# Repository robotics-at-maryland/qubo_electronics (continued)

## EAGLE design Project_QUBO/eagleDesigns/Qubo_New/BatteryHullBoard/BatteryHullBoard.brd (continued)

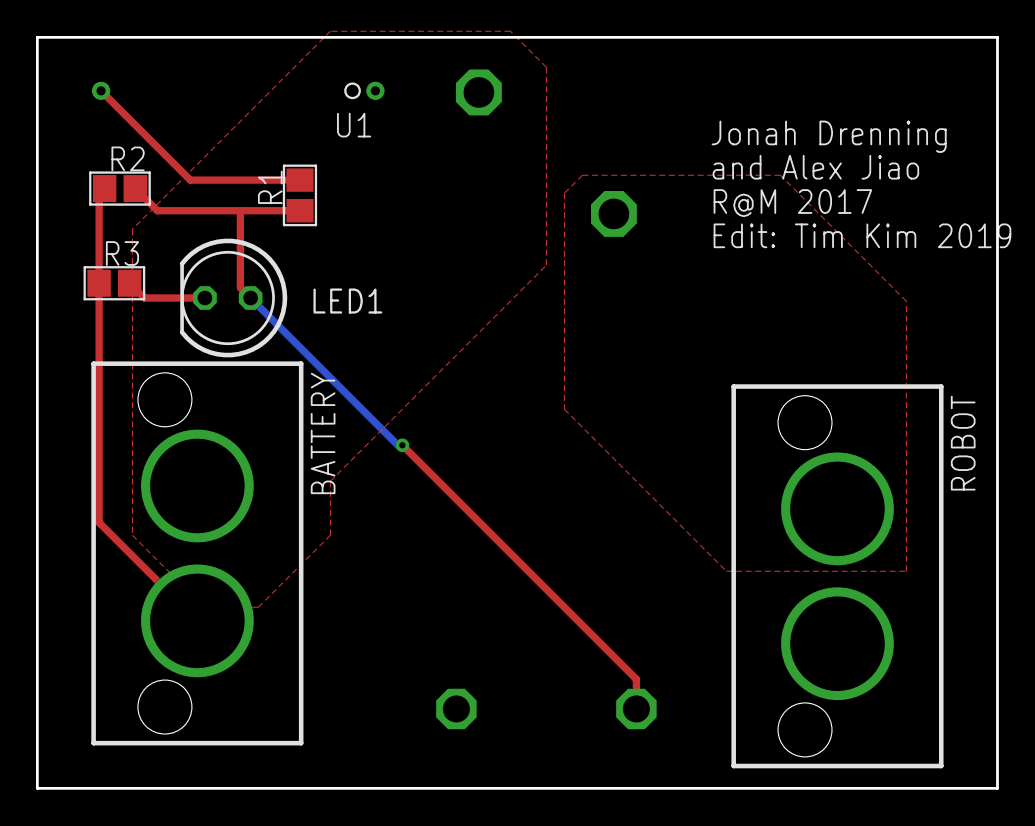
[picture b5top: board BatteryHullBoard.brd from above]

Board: 2 copper layers, 53.3 x 41.7 mm, 8 parts (0 on the bottom side), 6 nets.

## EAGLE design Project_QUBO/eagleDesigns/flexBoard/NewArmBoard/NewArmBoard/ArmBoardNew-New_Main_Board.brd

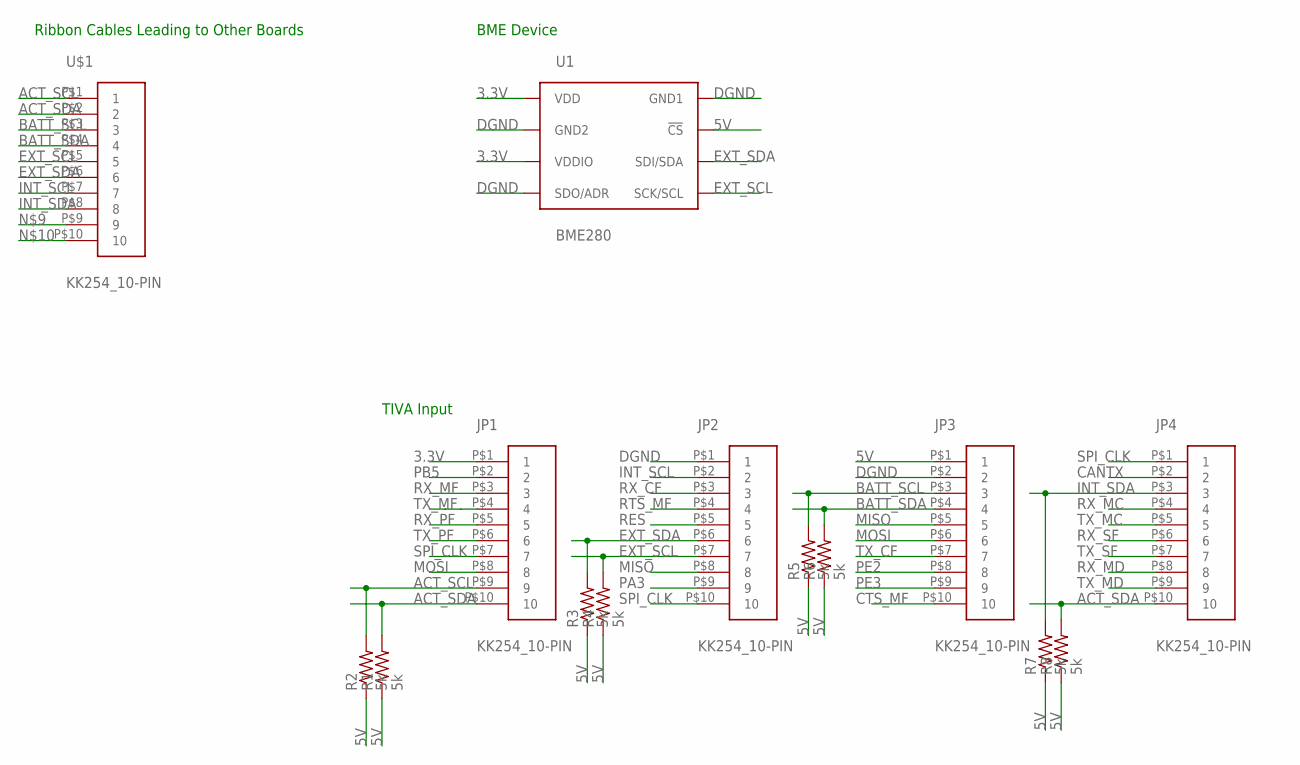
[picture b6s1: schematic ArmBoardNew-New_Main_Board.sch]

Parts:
JP1, JP2, JP3, JP4: KK254_10-PIN
R1, R2, R3, R4, R5, R6, R7, R8: 5k; R0805
U1: BME280; BME280_LGA
U$1: KK254_10-PIN

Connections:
3.3V: JP1.P$1 (1), U1.P$6 (VDDIO), U1.P$8 (VDD)
5V: JP3.P$1 (1), R1.1, R2.1, R3.1, R4.1, R5.1, R6.1, R7.1, R8.1, U1.P$2 (!CS)
ACT_SCL: JP1.P$9 (9), R2.2, U$1.P$1 (1)
ACT_SDA: JP1.P$10 (10), JP4.P$10 (10), R1.2, R8.2, U$1.P$2 (2)
BATT_SCL: JP3.P$3 (3), R5.2, U$1.P$3 (3)
BATT_SDA: JP3.P$4 (4), R6.2, U$1.P$4 (4)
CANTX: JP4.P$2 (2)
CTS_MF: JP3.P$10 (10)
DGND: JP2.P$1 (1), JP3.P$2 (2), U1.P$1 (GND1), U1.P$5 (SDO/ADR), U1.P$7 (GND2)
EXT_SCL: JP2.P$7 (7), R4.2, U1.P$4 (SCK/SCL), U$1.P$5 (5)
EXT_SDA: JP2.P$6 (6), R3.2, U1.P$3 (SDI/SDA), U$1.P$6 (6)
INT_SCL: JP2.P$2 (2), U$1.P$7 (7)
INT_SDA: JP4.P$3 (3), R7.2, U$1.P$8 (8)
MISO: JP2.P$8 (8), JP3.P$5 (5)
MOSI: JP1.P$8 (8), JP3.P$6 (6)
PA3: JP2.P$9 (9)
PB5: JP1.P$2 (2)
PE2: JP3.P$8 (8)
PE3: JP3.P$9 (9)
RES: JP2.P$5 (5)
RTS_MF: JP2.P$4 (4)
RX_CF: JP2.P$3 (3)
RX_MC: JP4.P$4 (4)
RX_MD: JP4.P$8 (8)
RX_MF: JP1.P$3 (3)
RX_PF: JP1.P$5 (5)
RX_SF: JP4.P$6 (6)
SPI_CLK: JP1.P$7 (7), JP2.P$10 (10), JP4.P$1 (1)
TX_CF: JP3.P$7 (7)
TX_MC: JP4.P$5 (5)
TX_MD: JP4.P$9 (9)
TX_MF: JP1.P$4 (4)
TX_PF: JP1.P$6 (6)
TX_SF: JP4.P$7 (7)

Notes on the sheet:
TIVA Input
Ribbon Cables Leading to Other Boards
BME Device

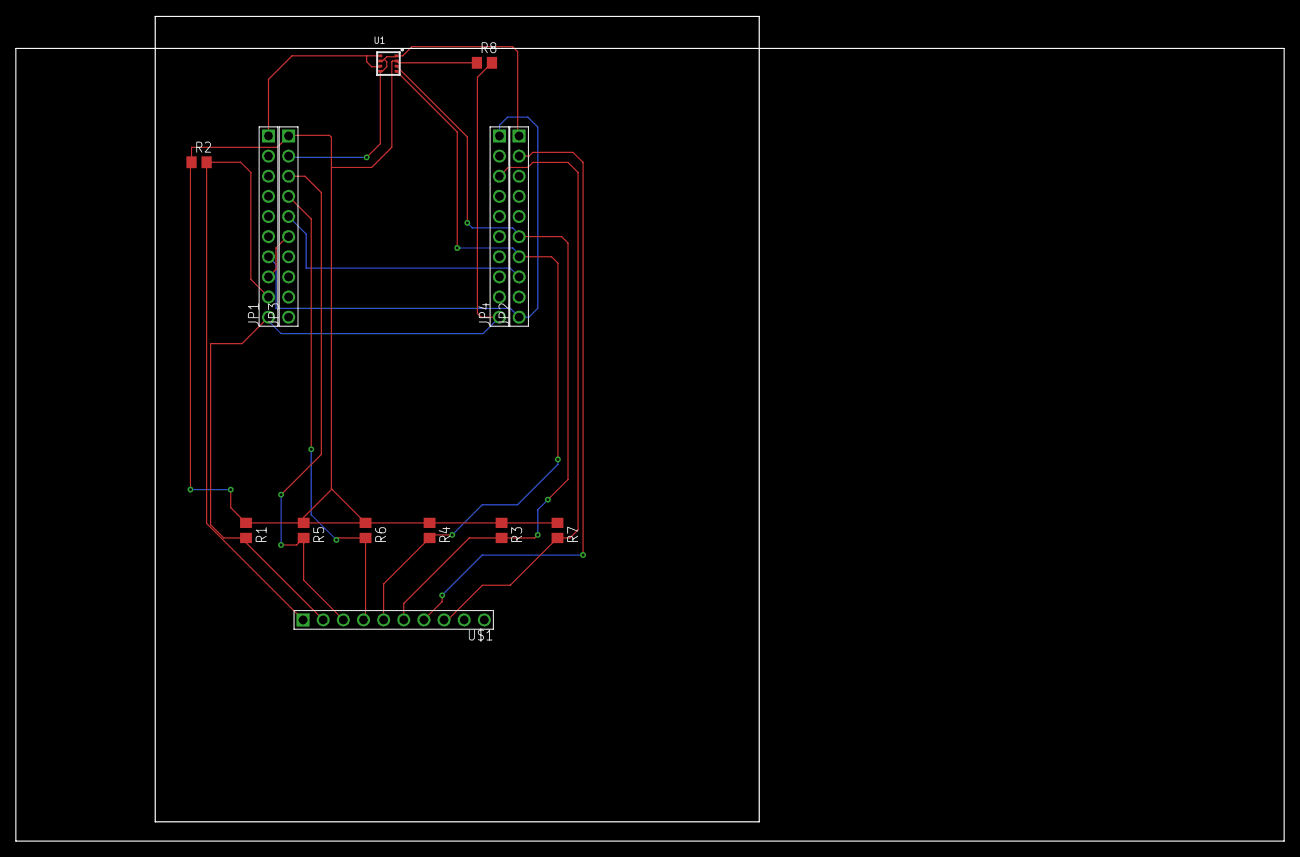
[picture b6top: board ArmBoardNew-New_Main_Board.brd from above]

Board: 2 copper layers, 160.0 x 104.0 mm, 14 parts (0 on the bottom side), 14 nets.

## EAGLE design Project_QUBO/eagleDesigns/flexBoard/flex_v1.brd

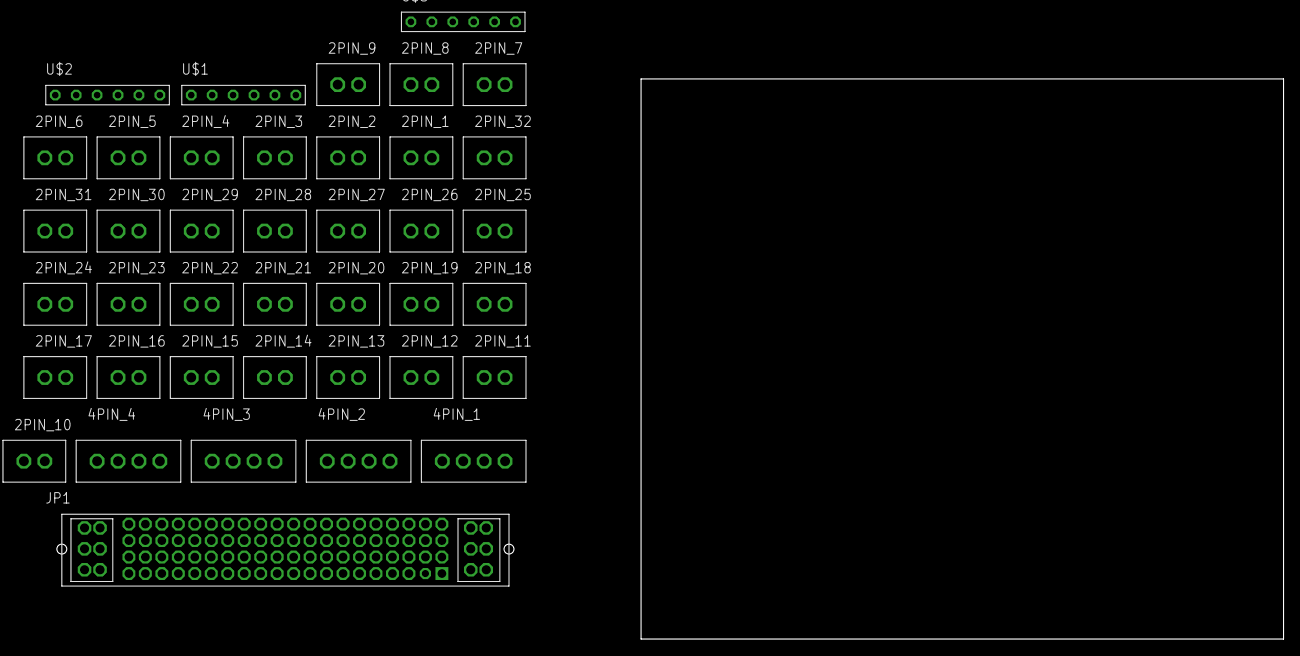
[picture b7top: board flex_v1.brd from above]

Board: 2 copper layers, 78.0 x 68.0 mm, 40 parts (0 on the bottom side), 6 nets, no tracks yet.

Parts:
2PIN_1, 2PIN_2, 2PIN_3, 2PIN_4, 2PIN_5, 2PIN_6, 2PIN_7, 2PIN_8, 2PIN_9, 2PIN_10, 2PIN_11, 2PIN_12, 2PIN_13, 2PIN_14, 2PIN_15, 2PIN_16, 2PIN_17, 2PIN_18, 2PIN_19, 2PIN_20, 2PIN_21, 2PIN_22, 2PIN_23, 2PIN_24, 2PIN_25, 2PIN_26, 2PIN_27, 2PIN_28, 2PIN_29, 2PIN_30, 2PIN_31, 2PIN_32: KK254_VERT_2PIN
4PIN_1, 4PIN_2, 4PIN_3, 4PIN_4: KK254_VERT_4PIN
JP1: MPSC-01-80
U$1, U$2, U$3: KK254_6PIN

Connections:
3V3: JP1.3, JP1.23, JP1.43, JP1.63
4_1_1: 2PIN_1.P$1, 2PIN_2.P$1, 2PIN_3.P$1, 2PIN_4.P$1, 2PIN_5.P$1, 2PIN_6.P$1, 2PIN_7.P$1, 2PIN_8.P$1, 2PIN_9.P$1, 2PIN_10.P$1, 2PIN_11.P$1, 2PIN_12.P$1, 2PIN_13.P$1, 2PIN_14.P$1, 2PIN_15.P$1, 2PIN_16.P$1, 2PIN_17.P$1, 2PIN_18.P$1, 2PIN_19.P$1, 2PIN_20.P$1, 2PIN_21.P$1, 2PIN_22.P$1, 2PIN_23.P$1, 2PIN_24.P$1, 2PIN_25.P$1, 2PIN_26.P$1, 2PIN_27.P$1, 2PIN_28.P$1, 2PIN_29.P$1, 2PIN_30.P$1, 2PIN_31.P$1, 2PIN_32.P$1
5V: JP1.2, JP1.22, JP1.42, JP1.62
12V: JP1.1, JP1.21, JP1.41, JP1.61
GND: JP1.4, JP1.12, JP1.15, JP1.18, JP1.24, JP1.33, JP1.34, JP1.36, JP1.37, JP1.39, JP1.40, JP1.44, JP1.64, JP1.P2,1, JP1.P2,2, JP1.P2,3, JP1.P2,4, JP1.P2,5, JP1.P2,6
V_BATT: JP1.P1,1, JP1.P1,2, JP1.P1,3, JP1.P1,4, JP1.P1,5, JP1.P1,6

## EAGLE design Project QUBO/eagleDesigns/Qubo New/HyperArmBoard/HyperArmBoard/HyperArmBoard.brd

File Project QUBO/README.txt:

This is the electronics folder for Project QUBO, the replacement for Tortuga 4.
===============================================================================

eagleLibraries is the library folder eagle.
	ALL robot PCB designs MUST only contain parts from libraries in the eagleLibraries directory.

datasheets is for all part datasheets used in the electronics designs.
	No subdirectories

eagleDesigns is for the actual eagle design files. 
	Subdirectories are created on a BOARD-BY-BOARD basis.
	If you're creating a new PCB, make a new folder. If you're editing an existing board, stay in the same folder.
	Use reason when creating new versions of files.

designDocumentation  is for design documentation.
	Use reason with file naming, no subdirectories.
	Document your design process ie. what your goal is, what options you considered, why you chose what you did, outline your final design selection, etc.
	Brownie points for LaTeX

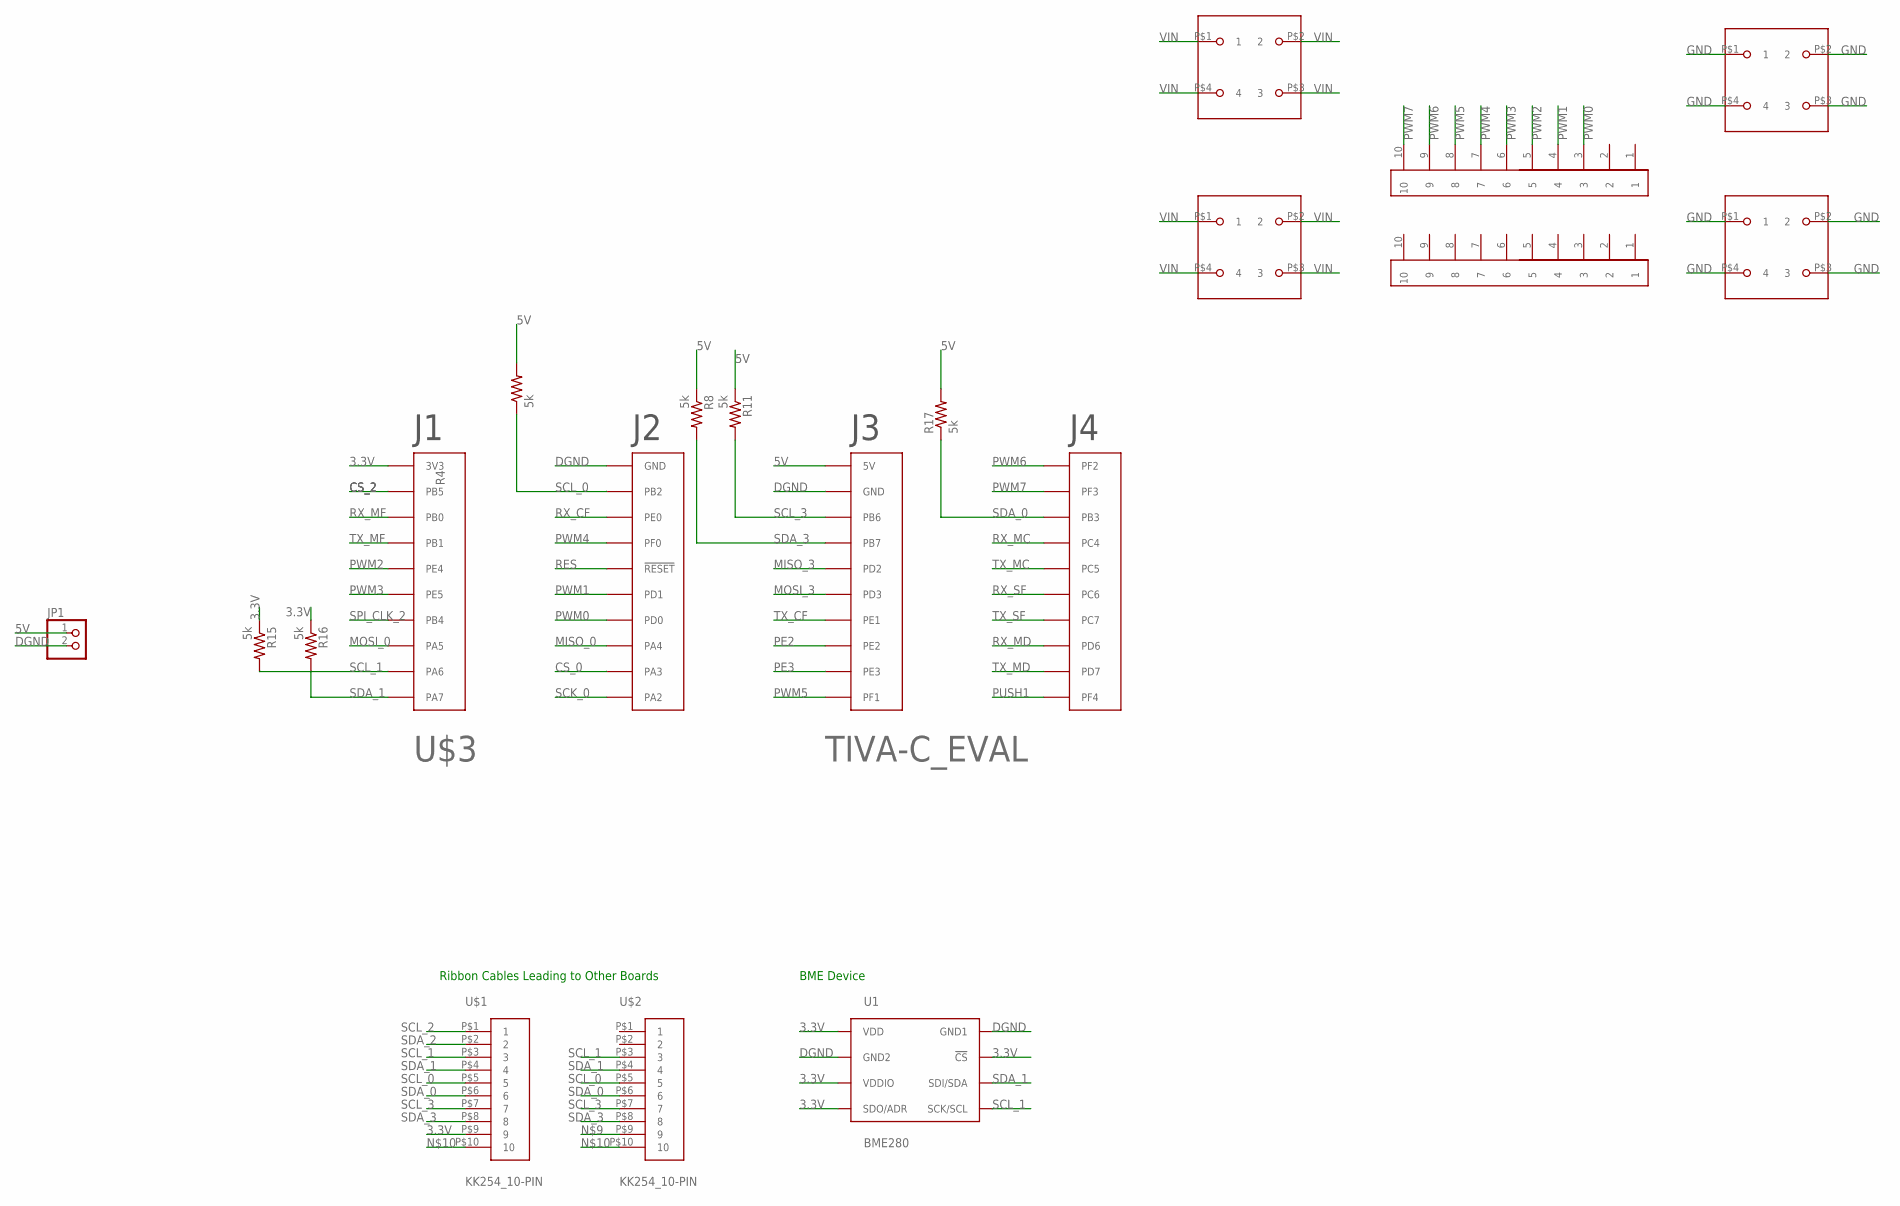
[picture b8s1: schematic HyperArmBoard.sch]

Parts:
JP1: PINHD-1X2; 1X02
R4, R8, R11, R15, R16, R17: 5k; R0805
U1: BME280; BME280_LGA
U$1, U$2: KK254_10-PIN
U$3: TIVA-C_EVAL
U$4, U$5, U$6, U$7: BCS-106-L-D-PE-BE; 4-PIN-BIGPOWER
U$10, U$11: CONN-RECEPT-2MM-VERT-AU-10POS; 10-PIN-LILPWR

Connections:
3.3V: R15.1, R16.1, U1.P$2 (!CS), U1.P$5 (SDO/ADR), U1.P$6 (VDDIO), U1.P$8 (VDD), U$1.P$9 (9), U$3.1-1 (3V3)
5V: JP1.1, R4.2, R8.1, R11.1, R17.2, U$3.3-1 (5V)
CS_0: U$3.2-9 (PA3)
CS_2: U$3.1-2 (PB5)
DGND: JP1.2, U1.P$1 (GND1), U1.P$7 (GND2), U$3.2-1 (GND), U$3.3-2 (GND)
GND: U$6.P$1 (1), U$6.P$2 (2), U$6.P$3 (3), U$6.P$4 (4), U$7.P$1 (1), U$7.P$2 (2), U$7.P$3 (3), U$7.P$4 (4)
MISO_0: U$3.2-8 (PA4)
MISO_3: U$3.3-5 (PD2)
MOSI_0: U$3.1-8 (PA5)
MOSI_3: U$3.3-6 (PD3)
unnamed: U$1.P$10 (10), U$2.P$10 (10)
PE2: U$3.3-8 (PE2)
PE3: U$3.3-9 (PE3)
PUSH1: U$3.4-10 (PF4)
PWM0: U$3.2-7 (PD0), U$10.3
PWM1: U$3.2-6 (PD1), U$10.4
PWM2: U$3.1-5 (PE4), U$10.5
PWM3: U$3.1-6 (PE5), U$10.6
PWM4: U$3.2-4 (PF0), U$10.7
PWM5: U$3.3-10 (PF1), U$10.8
PWM6: U$3.4-1 (PF2), U$10.9
PWM7: U$3.4-2 (PF3), U$10.10
RES: U$3.2-5 (!RESET!)
RX_CF: U$3.2-3 (PE0)
RX_MC: U$3.4-4 (PC4)
RX_MD: U$3.4-8 (PD6)
RX_MF: U$3.1-3 (PB0)
RX_SF: U$3.4-6 (PC6)
SCK_0: U$3.2-10 (PA2)
SCL_0: R4.1, U$1.P$5 (5), U$2.P$5 (5), U$3.2-2 (PB2)
SCL_1: R15.2, U1.P$4 (SCK/SCL), U$1.P$3 (3), U$2.P$3 (3), U$3.1-9 (PA6)
SCL_2: U$1.P$1 (1)
SCL_3: R11.2, U$1.P$7 (7), U$2.P$7 (7), U$3.3-3 (PB6)
SDA_0: R17.1, U$1.P$6 (6), U$2.P$6 (6), U$3.4-3 (PB3)
SDA_1: R16.2, U1.P$3 (SDI/SDA), U$1.P$4 (4), U$2.P$4 (4), U$3.1-10 (PA7)
SDA_2: U$1.P$2 (2)
SDA_3: R8.2, U$1.P$8 (8), U$2.P$8 (8), U$3.3-4 (PB7)
SPI_CLK_2: U$3.1-7 (PB4)
TX_CF: U$3.3-7 (PE1)
TX_MC: U$3.4-5 (PC5)
TX_MD: U$3.4-9 (PD7)
TX_MF: U$3.1-4 (PB1)
TX_SF: U$3.4-7 (PC7)
VIN: U$4.P$1 (1), U$4.P$2 (2), U$4.P$3 (3), U$4.P$4 (4), U$5.P$1 (1), U$5.P$2 (2), U$5.P$3 (3), U$5.P$4 (4)

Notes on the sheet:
Ribbon Cables Leading to Other Boards
BME Device

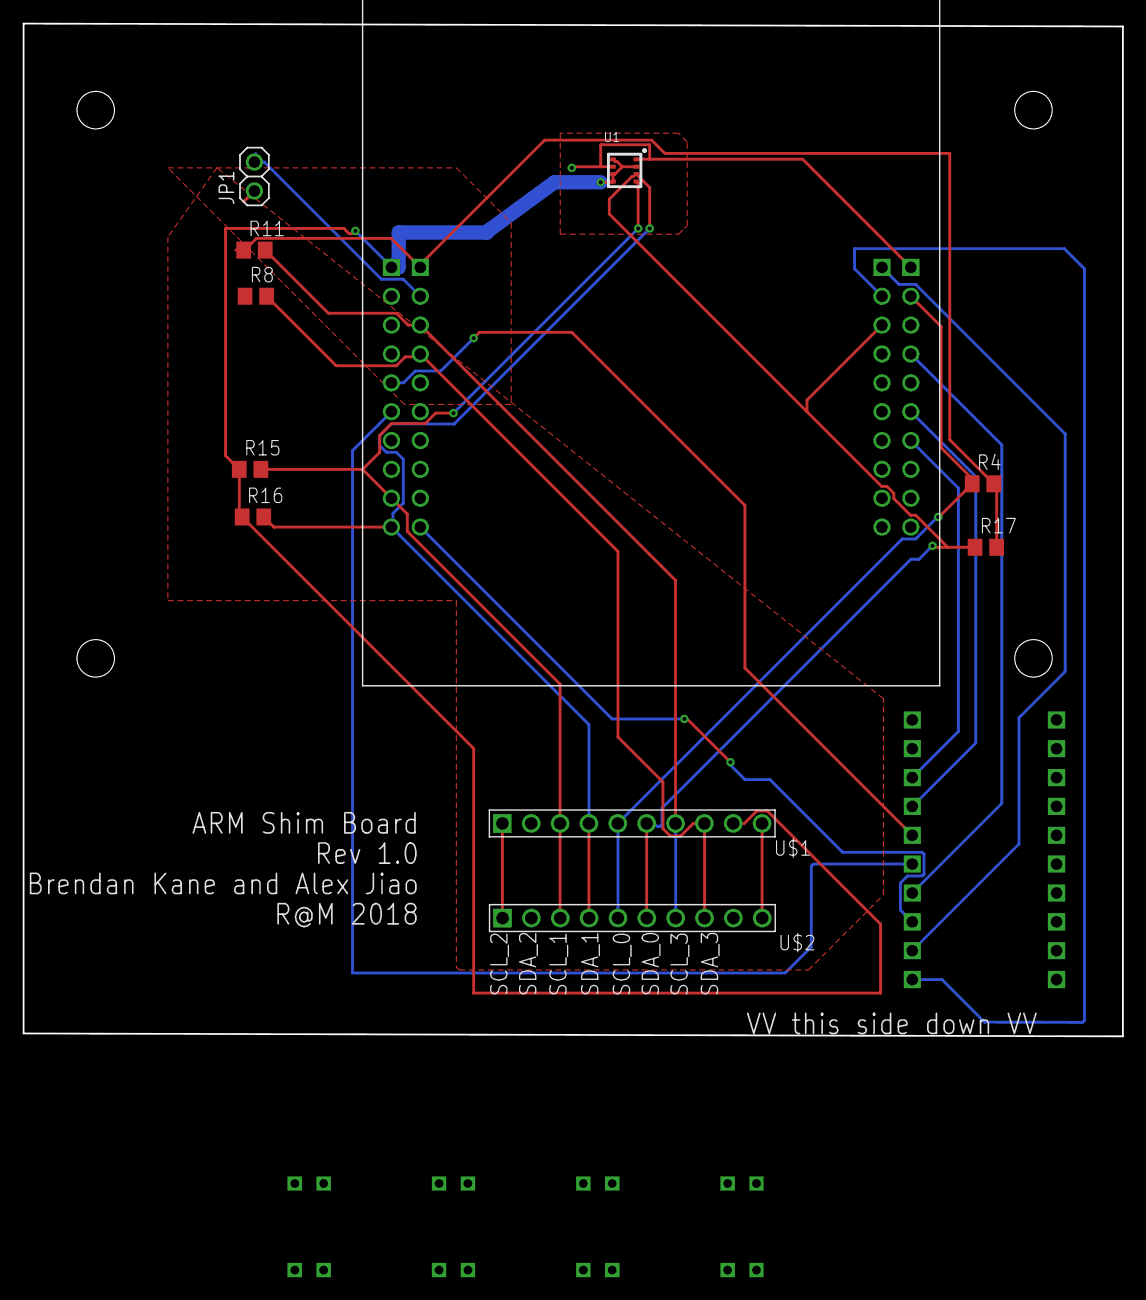
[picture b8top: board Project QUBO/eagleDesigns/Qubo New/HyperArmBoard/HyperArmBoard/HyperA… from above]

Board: 2 copper layers, 96.8 x 89.2 mm, 17 parts (0 on the bottom side), 20 nets.

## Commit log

2016-09-08 initial commit: added Project QUBO folder
2016-09-08 edited readme.md
2016-09-13 created readme
2016-09-21 updated psb sch
2016-09-25 added UWE to murata.lbr
2016-10-02 edited power supply board sch
2016-10-25 made new sch of power board to start anew
2016-10-26 added ltc2497 symbol to linear.lbr
2016-10-28 finished ADC CAD
2016-11-16 added zener diode
2016-11-17 added pullup-pulldown resistor config for i2c addressing
2016-11-18 added new zener diode and mosfet
2016-11-18 added diode OR/ hot swap to schematic
2016-11-19 updated psb .sch
2016-11-21 finished diode or/ hot swap on powerBoard/powerSupplyBoard_new.sch
2016-11-22 psb schematic updates
2016-11-23 edited motor board
2016-11-23 added LED placeholder
2016-11-23 update to motor control board
    linked current sensor to header, ADC, for one motor. added ultrafit
    (motor power) and supersabre (batery power) headers
2016-11-29 remove lock
2016-11-30 update to MCB
    need to finalize pinouts on ADC and PWM controller, filer capacitors on
    current sensors, fuses
2016-12-02 psb updates
2016-12-07 edits to powerBoard/powerSupplyBoard_new.sch
2017-01-27 add filter caps
2017-01-27 create motor control board board
2017-01-27 finalize MCB
    Devices still need to have packages designed. Pneumatics board still
    needs to be integrated
2017-01-27 minor changed to board
2017-02-01 fixed psb brd errors
2017-02-03 added ultrafit
2017-02-05 placed everything preliminarily
2017-02-08 psb layout updates
2017-02-10 combined pneumatics and MCB
2017-02-10 got rid of sense resistor on psb
2017-02-13 added new mosfet
2017-04-04 deleted lock files
2017-04-04 pls god
2017-04-04 Cleaned up lbr folder
2017-04-04 Library updates
2017-04-06 Charging board layout, rev. 1
2017-04-06 finishing touches on oring board
2017-04-07 Final Design
2017-04-07 Added INA219 voltage sensors.
2017-04-08 Charging board version 1 - completed
2017-04-12 Added libs
2017-04-12 Updated libraries
2017-04-13 Main switch added to Jr Support.
2017-04-18 Created breadboards. Added 5V reg PG fault line.
2017-04-18 Updated VS pin on INA219s to 5V
2017-04-19 "breadboad" updates.
2017-07-01 updated jr support
2017-08-08 Final update from Ben - updated documentation, electrical schematics and board layouts, and Eagle libraries.
2017-09-21 added text file
2017-10-02 Updated PTN78020 footprint (corrected Ales's incompetence)
2017-10-12 power board
2017-10-13 Added the voltage divider's to the battery balancing board and updated the part's list
2017-10-13 Reorganized the powerBoard folder
2017-10-13 Added a .txt file showing all calculations for the board
2017-10-17 Added supporting components for the SHDN pin to the schematic and part's list
2017-10-23 Changed some values for the OV and UV pins
2017-10-27 Added a description of all the LTC4364 functionality (LTC4364 Notes.txt)
2017-11-07 Added the IRF7458PbF N-Channel MOSFET SMD Footprint to eagleLibraries
2017-11-27 reed switch
2017-11-30 I created a new version of NewArmBoard
2017-12-05 added io expander to texas.lbr
2017-12-07 formatted power board schematic layout
2017-12-07 committing backup files
2018-01-20 updated armboard schematic and brd layout
2018-01-22 created gerbers for arm board
2018-01-25 Redesigned the battery balancing board
2018-01-25 Added the spice simulation circuit to the the powerBoard directory
2018-01-28 added UEI to murata.lbr
2018-02-02 PCB Layout complete
2018-02-08 Battery Balancing Board Layout
2018-02-16 Finished PCB Layout for Battery Balancing Board
2018-02-17 Revised the board layout
2018-02-18 Add the Traco Power TSR 2-2450 DC/DC Converter to a new Traco Power library.
2018-02-20 Alex is my lover
2018-02-21 Added connectors
    I added a device for a row of 10 low power pins and another device for a block of 4 high power pin.
2018-02-21 Finished Parts List
2018-02-21 Added Designed and Reviewed by messages to the silkscreen
2018-02-23 She gonna be thicccc
2018-02-28 Hypertonics board building
    I built a lot of the hypertonics board
2018-02-28 I added a maybe useful cam voltage source
2018-02-28 Nevermind, no camera voltage source
2018-02-28 Power board changes
    worked on layout and routing of power board
2018-03-02 PowerBoard update
    Updated powerboard wiring, and resized.
2018-03-09 Finished PowerboardRev1
    Revision 1 of the Powerboard
2018-03-09 I did a cam
    I did a cam on the hypertonics board
2018-03-09 fixing version controls
2018-03-13 Powerboard parts
    Added a parts excel spreadsheet for powerboard
2018-03-16 Updated powerboard spreadsheet
    ^^
2018-03-18 Finished Powerboard Spreadsheet
    It is done
2018-03-28 Capacitor and Powerboard
    Added capacitor package and adjusted powerboard
2018-03-29 edited the parts spreadsheet
2018-09-13 Nothing, this is a test
    Im testing if this works
2018-09-25 I just named some pins
    I named some pins to make my life easier on a board later
2018-09-26 this power board should be fixed
    I had to fix anthony's screwed up board
2018-10-02 Fix to powerboard
    Minor errors corrected to power board
2018-10-16 misc
    some small relabling of a board or two and I retrieved a fixed version of the formerly broken arm board
2018-10-31 started symbol for arduino teensy 3.5
2018-11-01 i made more progress on the Teensy package
    I added all these lill pins
2018-11-01 first draft for Teensy's symbol
2018-11-01 small edit to teensy
2018-11-08 Stole some dudes footprint
    YOINK
2018-11-14 maxim11049 device
2018-11-14 adfas
2018-11-27 i hate svn
2019-02-15 Changed diamter of holes on terminals to 40 mm and added routes from sda and sclto LIL_PWR terminal
2019-02-24 Prolly random fixes
    I don't remember but it's probaly pretty good
2019-02-24 Fixes to TIVA board
    Some of the pins were named wrong so I fixed them
2019-02-24 Resolved merge conflict by incorporating both suggestions.
2019-02-24 minor hypertonix edits
    I changed the names of some headers and made some curved traces not curved
2019-02-24 Changes to Tiva board
    I had to rewire some things
2019-03-13 Changed Relay on BatteryHubBoard with new one
2019-03-13 Added new relay footprint ADJH21112 and modified batteryhullboard
2019-04-25 armboard modifications
2019-04-25 added gitignore
2020-02-21 HyperArmBoard was designed.
2020-02-29 created HyperArmboard
2020-02-29 test
2020-07-31 made hyperarmboard
    made newboard thatcombindes the hypertonics and arm board
2020-09-23 changes to hyperarm and power board
2020-10-15 fixingsynchronicity issues
